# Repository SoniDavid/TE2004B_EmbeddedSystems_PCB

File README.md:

# TE2004B_EmbeddedSystems_PCB

This repository contains custom KiCad libraries for embedded systems PCB design, including symbol libraries and footprint libraries for ESP32-C3 SuperMini, STM32 Nucleo-F767ZI, and various sensors and components.

## Project Structure

- **PCBEmbebidosLibSymbol/** - Custom symbol library folder
  - `ESP32-C3_SUPERMINI_TH.kicad_sym` - ESP32-C3 SuperMini symbols
  - `NUCLEO-F767ZI.kicad_sym` - STM32 Nucleo-F767ZI symbols

- **PCBEmebebidosLibFootPrint.pretty/** - Custom footprint library folder
  - Contains footprints for battery, ESC, MCP2515, ESP32-C3, motor encoder, MPU9250, regulators, servo, STM32, and TJA1051

## How to Import Libraries into KiCad

### Importing Symbol Libraries

1. Open KiCad and go to **Preferences** → **Manage Symbol Libraries...**

2. In the Symbol Libraries dialog, click on the **Project Specific Libraries** tab (if you want the library only for this project) or **Global Libraries** tab (if you want it available for all projects)

3. Click the **folder icon** (Browse Libraries) at the bottom of the window

4. Navigate to the `PCBEmbebidosLibSymbol` folder in this repository

5. Select the symbol files you want to add:
   - `ESP32-C3_SUPERMINI_TH.kicad_sym`
   - `NUCLEO-F767ZI.kicad_sym`

6. Click **Open** and then **OK**

### Importing Footprint Libraries

1. Open KiCad and go to **Preferences** → **Manage Footprint Libraries...**

2. In the Footprint Libraries dialog, click on the **Project Specific Libraries** tab (if you want the library only for this project) or **Global Libraries** tab (if you want it available for all projects)

3. Click the **+** icon at the bottom to add a new library entry

## Available Components

### Symbols
- ESP32-C3 SuperMini (Through-Hole)
- STM32 Nucleo-F767ZI

### Footprints
- Battery connector
- ESC (Electronic Speed Controller)
- MCP2515 CAN controller
- ESP32-C3 SuperMini module
- Motor with encoder
- MPU9250 IMU sensor
- Voltage regulator
- Servo motor connector
- STM32 Nucleo-F767ZI
- TJA1051 CAN transceiver

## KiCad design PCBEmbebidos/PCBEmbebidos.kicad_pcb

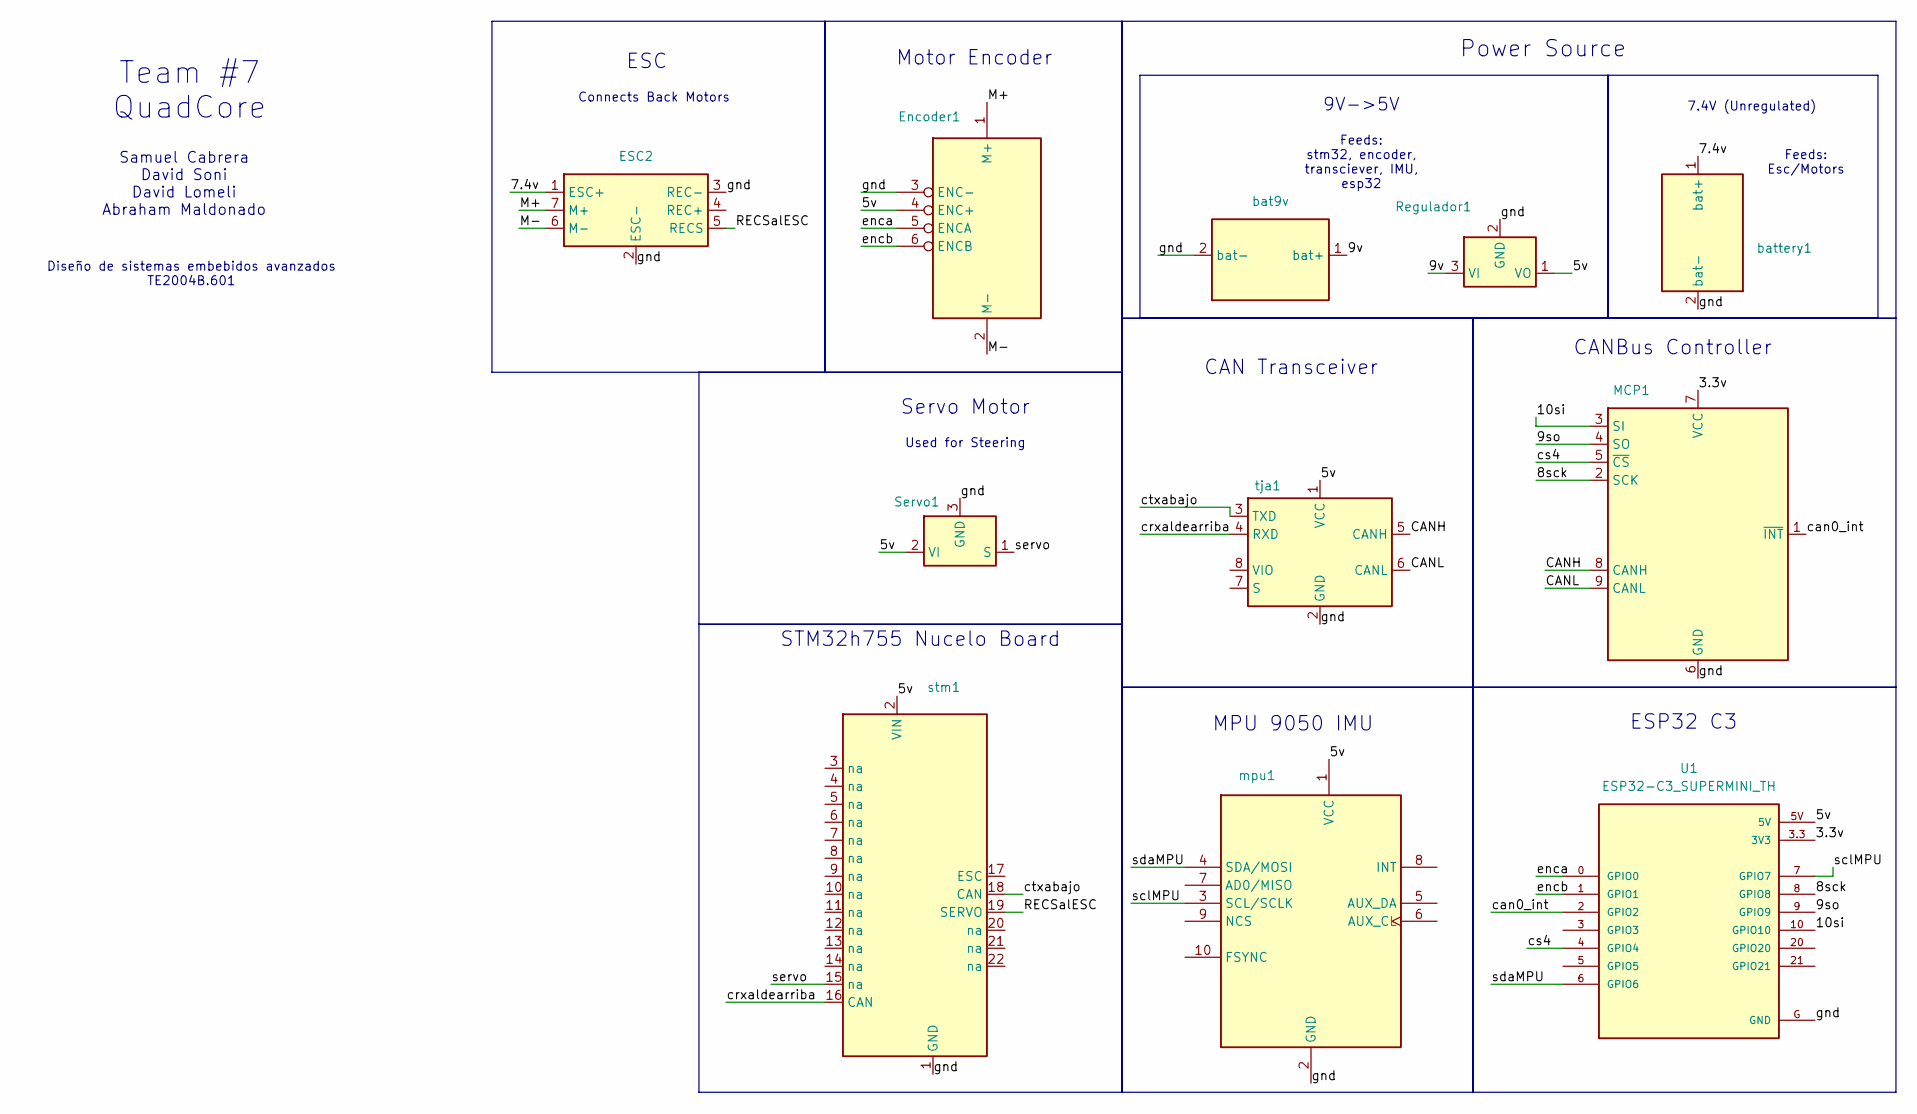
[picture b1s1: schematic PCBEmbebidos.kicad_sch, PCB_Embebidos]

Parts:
ESC2: ESC
Encoder1: `motorEncoder
MCP1: mcp2515perobienimg
Regulador1: Regulador
Servo1: Servo
U1: ESP32-C3_SUPERMINI_TH; MODULE_ESP32-C3_SUPERMINI_TH
bat1: bat9v; battery
battery1: battery
mpu1: mpu9250bien
stm1: stm32imgbien
tja1: tja1051img

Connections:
/3.3v: MCP1.7 (VCC), U1.3.3 (3V3)
/5v: Encoder1.4 (ENC+), Regulador1.1 (VO), Servo1.2 (VI), U1.5V, mpu1.1 (VCC), stm1.2 (VIN), tja1.1 (VCC)
/7.4v: ESC2.1 (ESC+), battery1.1 (bat+)
/8sck: MCP1.2 (SCK), U1.8 (GPIO8)
/9so: MCP1.4 (SO), U1.9 (GPIO9)
/9v: Regulador1.3 (VI), bat1.1 (bat+)
/10si: MCP1.3 (SI), U1.10 (GPIO10)
/CANH: MCP1.8 (CANH), tja1.5 (CANH)
/CANL: MCP1.9 (CANL), tja1.6 (CANL)
/M+: ESC2.7 (M+), Encoder1.1 (M+)
/M-: ESC2.6 (M-), Encoder1.2 (M-)
/RECSalESC: ESC2.5 (RECS), stm1.19 (SERVO)
/can0_int: MCP1.1 (~INT), U1.2 (GPIO2)
/crxaldearriba: stm1.16 (CAN), tja1.4 (RXD)
/cs4: MCP1.5 (~CS), U1.4 (GPIO4)
/ctxabajo: stm1.18 (CAN), tja1.3 (TXD)
/enca: Encoder1.5 (ENCA), U1.0 (GPIO0)
/encb: Encoder1.6 (ENCB), U1.1 (GPIO1)
/gnd: ESC2.2 (ESC-), ESC2.3 (REC-), Encoder1.3 (ENC-), MCP1.6 (GND), Regulador1.2 (GND), Servo1.3 (GND), U1.G (GND), bat1.2 (bat-), battery1.2 (bat-), mpu1.2 (GND), stm1.1 (GND), tja1.2 (GND)
/sclMPU: U1.7 (GPIO7), mpu1.3 (SCL/SCLK)
/sdaMPU: U1.6 (GPIO6), mpu1.4 (SDA/MOSI)
/servo: Servo1.1 (S), stm1.15 (na)

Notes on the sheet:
Diseño de sistemas embebidos avanzados TE2004B.601
Samuel Cabrera David Soni David Lomeli Abraham Maldonado
Feeds: stm32, encoder, transciever, IMU, esp32
ESP32 C3
9V->5V
ESC
Motor Encoder
Team #7 QuadCore
CANBus Controller
STM32h755 Nucelo Board
Power Source
Used for Steering
Servo Motor
CAN Transceiver
Feeds: Esc/Motors
Connects Back Motors
7.4V (Unregulated)
MPU 9050 IMU

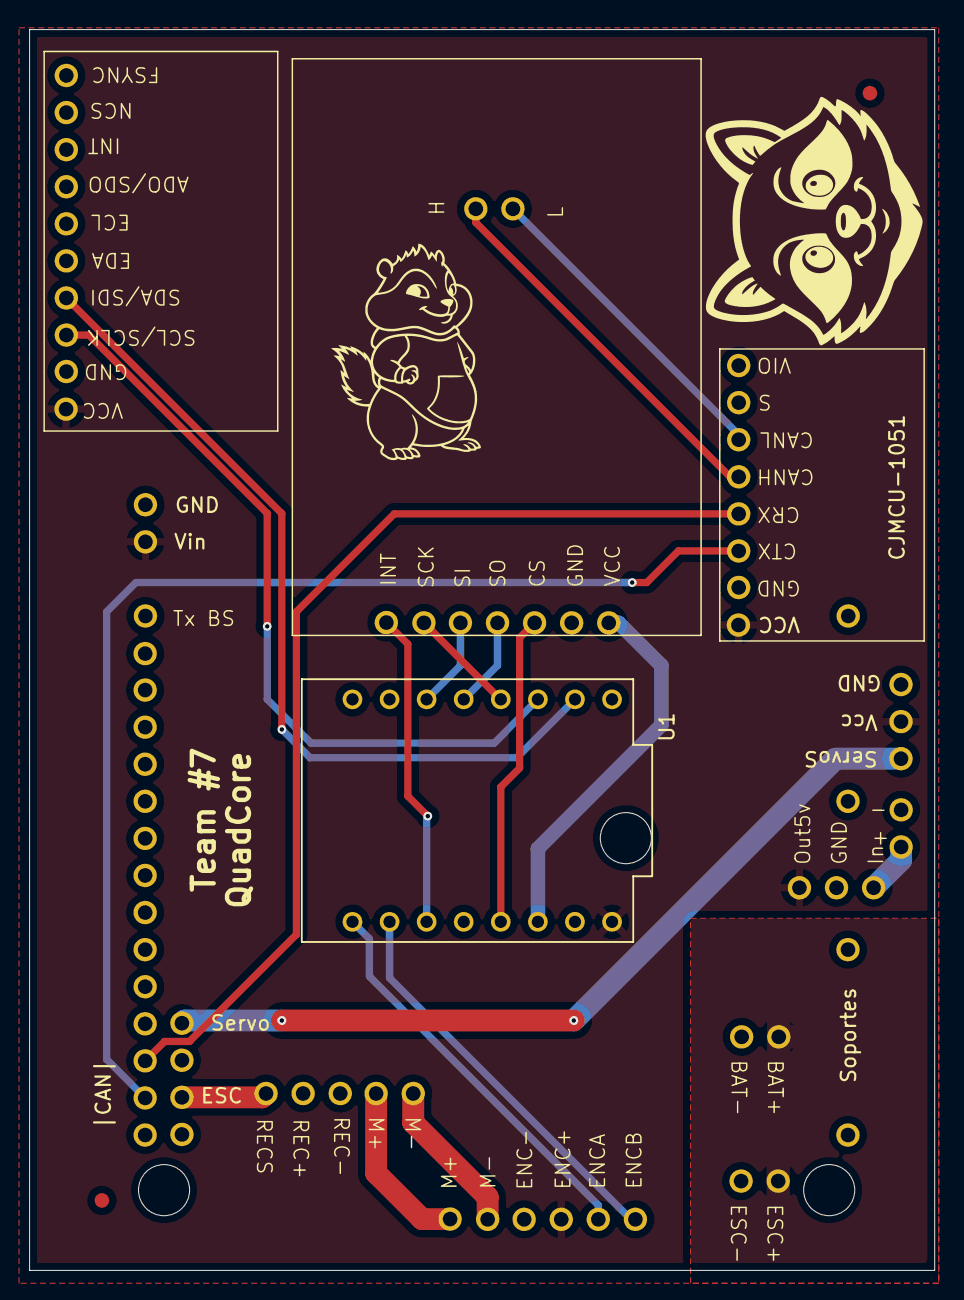
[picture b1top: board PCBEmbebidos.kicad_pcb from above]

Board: 2 copper layers, 62.0 x 85.0 mm, 11 parts (0 on the bottom side), 22 nets.

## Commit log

2025-11-19 Upload full PCB
